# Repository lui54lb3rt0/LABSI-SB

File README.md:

# LABSI Project
## Description of project
This project has made part of the LABSI Class of my BSc in Electrical and Computer Engineer degree and consists of a self-balancing robot.

## The robot :robot: 

The robot has made with several components from old label printers and mechanical trash.

The robot has two wheels attached to the stepper motors that are capable to move forward and backward the robot with PWM generated in the function of GYRO and Accelerometer positions from a PID controller developed to the uC.

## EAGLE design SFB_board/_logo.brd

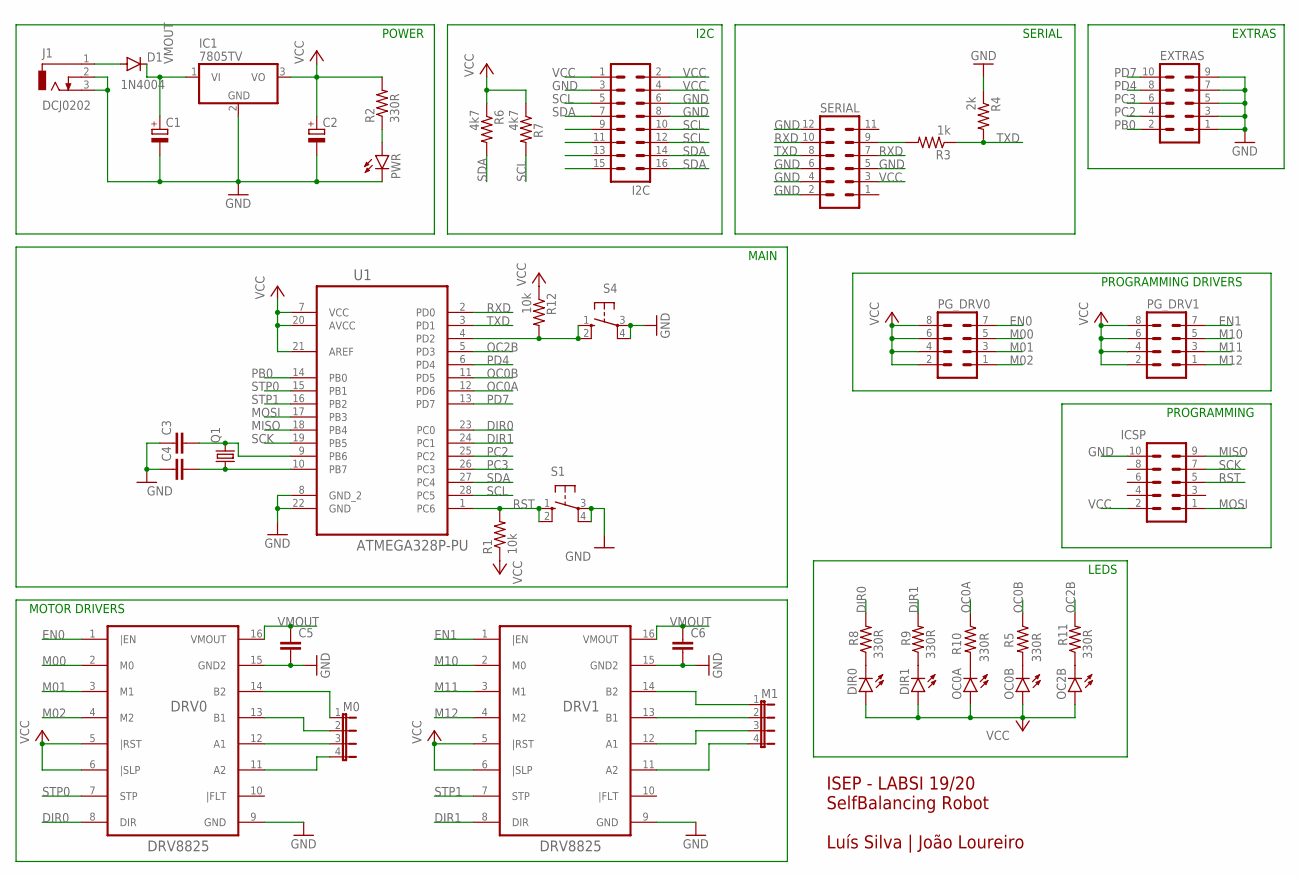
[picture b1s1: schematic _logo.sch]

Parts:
C1, C2: CPOL-EUB45181A; B45181A
C3, C4: C5/3; C5B3
C5, C6: C2.5/2; C2.5-2
D1: 1N4004; DO41-10
DIR0, DIR1: LED3MM
DRV0, DRV1: DRV8825
EXTRAS: ML10
I2C: MA08-2
IC1: 7805TV; TO220V
ICSP: ML10
J1: DCJ0202
M0, M1: JP4E; JP4
OC0A, OC0B, OC2B: LED3MM
PG_DRV0, PG_DRV1: MA04-2
PWR: LED3MM
Q1: CRYSTALHC49S; HC49/S
R1, R12: 10k; 0207/10
R2, R5, R8, R9, R10, R11: 330R; 0207/10
R3: 1k; 0207/10
R4: 2k; 0207/10
R6, R7: 4k7; 0207/10
S1, S4: 10-XX; B3F-10XX
SERIAL: MA06-2
U1: ATMEGA328P-PU; DIP254P762X457-28

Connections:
DIR0: DRV0.8 (DIR), R8.2, U1.23 (PC0)
DIR1: DRV1.8 (DIR), R9.2, U1.24 (PC1)
EN0: DRV0.1 (|EN), PG_DRV0.7
EN1: DRV1.1 (|EN), PG_DRV1.7
GND: C1.-, C2.-, C3.1, C4.1, C5.2, C6.2, DRV0.9 (GND), DRV0.15 (GND2), DRV1.9 (GND), DRV1.15 (GND2), EXTRAS.1, EXTRAS.3, EXTRAS.5, EXTRAS.7, EXTRAS.9, I2C.3, I2C.6, I2C.8, IC1.2 (GND), ICSP.10, J1.2, J1.3, PWR.K (C), R4.1, S1.3, S1.4 (P1), S4.3, S4.4 (P1), SERIAL.2, SERIAL.4, SERIAL.5, SERIAL.6, SERIAL.12, U1.8 (GND_2), U1.22 (GND)
M00: DRV0.2 (M0), PG_DRV0.5
M01: DRV0.3 (M1), PG_DRV0.3
M02: DRV0.4 (M2), PG_DRV0.1
M10: DRV1.2 (M0), PG_DRV1.5
M11: DRV1.3 (M1), PG_DRV1.3
M12: DRV1.4 (M2), PG_DRV1.1
MISO: ICSP.9, U1.18 (PB4)
MOSI: ICSP.1, U1.17 (PB3)
unnamed: DRV0.14 (B2), M0.1
unnamed: PWR.A, R2.1
unnamed: D1.A, J1.1
unnamed: C4.2, Q1.1, U1.10 (PB7)
unnamed: C3.2, Q1.2, U1.9 (PB6)
unnamed: R3.2, SERIAL.9
unnamed: OC0B.K (C), R5.2
unnamed: DIR0.K (C), R8.1
unnamed: DIR1.K (C), R9.1
unnamed: OC0A.K (C), R10.2
unnamed: OC2B.K (C), R11.1
unnamed: DRV0.13 (B1), M0.2
unnamed: DRV0.12 (A1), M0.3
unnamed: DRV0.11 (A2), M0.4
unnamed: DRV1.14 (B2), M1.1
unnamed: DRV1.13 (B1), M1.2
unnamed: DRV1.12 (A1), M1.3
unnamed: DRV1.11 (A2), M1.4
OC0A: R10.1, U1.12 (PD6)
OC0B: R5.1, U1.11 (PD5)
OC2B: R11.2, U1.5 (PD3)
PB0: EXTRAS.2, U1.14 (PB0)
PC2: EXTRAS.4, U1.25 (PC2)
PC3: EXTRAS.6, U1.26 (PC3)
PD4: EXTRAS.8, U1.6 (PD4)
PD7: EXTRAS.10, U1.13 (PD7)
RST: ICSP.5, R1.2, S1.1 (S), S1.2 (S1), U1.1 (PC6)
RST1: R12.2, S4.1 (S), S4.2 (S1), U1.4 (PD2)
RXD: SERIAL.7, SERIAL.10, U1.2 (PD0)
SCK: ICSP.7, U1.19 (PB5)
SCL: I2C.5, I2C.10, I2C.12, R7.2, U1.28 (PC5)
SDA: I2C.7, I2C.14, I2C.16, R6.2, U1.27 (PC4)
STP0: DRV0.7 (STP), U1.15 (PB1)
STP1: DRV1.7 (STP), U1.16 (PB2)
TXD: R3.1, R4.2, SERIAL.8, U1.3 (PD1)
VCC: C2.+, DIR0.A, DIR1.A, DRV0.5 (|RST), DRV0.6 (|SLP), DRV1.5 (|RST), DRV1.6 (|SLP), I2C.1, I2C.2, I2C.4, IC1.3 (VO), ICSP.2, OC0A.A, OC0B.A, OC2B.A, PG_DRV0.2, PG_DRV0.4, PG_DRV0.6, PG_DRV0.8, PG_DRV1.2, PG_DRV1.4, PG_DRV1.6, PG_DRV1.8, R1.1, R2.2, R6.1, R7.1, R12.1, SERIAL.3, U1.7 (VCC), U1.20 (AVCC), U1.21 (AREF)
VMOUT: C1.+, C5.1, C6.1, D1.C, DRV0.16 (VMOUT), DRV1.16 (VMOUT), IC1.1 (VI)

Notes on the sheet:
POWER
PROGRAMMING
ISEP - LABSI 19/20 SelfBalancing Robot Luís Silva | João Loureiro
I2C
SERIAL
EXTRAS
PROGRAMMING DRIVERS
LEDS
MAIN
MOTOR DRIVERS

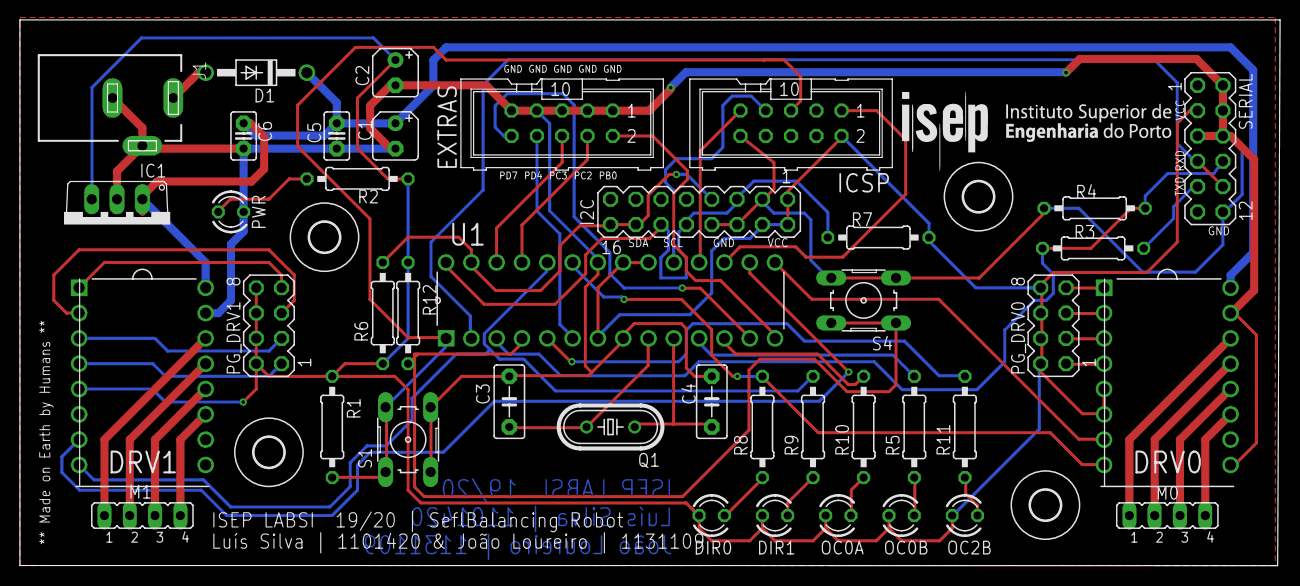
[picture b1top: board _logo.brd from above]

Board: 2 copper layers, 126.5 x 54.8 mm, 45 parts (0 on the bottom side), 50 nets.

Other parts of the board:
U$1, U$2, U$3, U$4: 3,0

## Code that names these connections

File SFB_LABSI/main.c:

/********************************************************
Language            :      C
Year                :      2019/2020
Class               :      LABSI
Authors             :      Luis Silva | Joao Loureiro
E-mail              :      1101420@isep.ipp.pt | 1131109@isep.ipp.pt
*********************************************************/

#define F_CPU 16000000UL								/* Define CPU clock Frequency e.g. here its 16MHz */
#include <avr/io.h>										/* Include AVR std. library file */
#include <avr/interrupt.h>								/* Include AVR interrupt library file */
#include <util/delay.h>									/* Include delay header file */
#include <inttypes.h>									/* Include integer type header file */
#include <stdlib.h>										/* Include standard library file */
#include <stdio.h>
#include <stdint.h>
#include "MPU6050_res_define.h"							/* Include MPU6050 register define file */
#include "I2C_Master_H_file.h"							/* Include I2C Master header file */

typedef struct USARTRX
{
	char receiver_buffer;
	unsigned char status;
	unsigned char receive 	: 1;
	unsigned char error	: 1;

}USARTRX_st;

volatile USARTRX_st rxUSART = {0,0,0,0};
char TxBuffer[50];
char float_[10];

/* Functions */

void SendMessage(char * buffer)
{
	unsigned char i=0;
	while(buffer[i]!='\0')
	{
		while((UCSR0A & 1<<UDRE0)==0);
		UDR0=buffer[i];
		i++;
	}
}

volatile uint8_t timerFlag = 0;
volatile float Acc_x,Acc_y,Acc_z,Temperature,Gyro_x,Gyro_y,Gyro_z;
volatile int ledCounter = 0;

float Acceleration_angle[2];
float Gyro_angle[2];
float Total_angle[2];

float elapsedTime = 0.001408;							//TS - time sample
float rad_to_deg = 180/3.141592654;

int PWM, error, previous_error;
float pid_p=0;
float pid_i=0;
float pid_d=0;
float pid_tot=0;
float previous_pid_tot = 0;

/////////////////PID CONSTANTS/////////////////
float kp = 0;
float ki = 0;
float kd = 0;
///////////////////////////////////////////////

float desired_angle = 0;								//This is the angle in which we want the balance to stay steady

/* Functions start here */
void inic()
{
	
	DDRC = 0x0F;										// Set PC0 & PC1 as output to Motor direction & scope test probes
	DDRB = 0x06;										// Set PB1 and PB2 as output OC1A & OC1B
	DDRD = (1<<DDD3) | (1<<DDD4) | (1<<DDD5) | (1<<DDD6) ;

	PORTD = (0<<DDD2) | (1<<DDD3)  | (1<<DDD5) | (1<<DDD6);
	PORTC = 0b00000011;

	/* Timer 1 */
	TCCR1A = ((1 << COM1A0) | (1 << COM1B0));			// Enable OC1A e OC1B to motors
	TCCR1B = ((1 << CS12) | (1 << WGM12));				// CLKIO/256 (From prescaler) | Mode CTC
	OCR1A = 65535;										// motor speed right
	OCR1B = 65535;										// motor speed left


	/* Timer 2 */
	TCCR2A = (1<<WGM21);								// MODE CTC
	TCCR2B = ((1 << CS21) | (1 << CS22));				// CLKIO/256 (From prescaler)
	TIMSK2 = (1 << OCIE2A);								// Enable TIMER0
	OCR2A = 88;											// ~0.001088s  ~900Hz    68

	/* USART */
	UBRR0H=0;
	UBRR0L=51;											// BAUDRATE 38400
	UCSR0A=(1<<U2X0);									// Double Speed
	UCSR0B=(1<<RXCIE0)|(1<<RXEN0)|(1<<TXEN0);			// RX Complete Interrupt Enable, Receiver Enable; transmite Enable
	UCSR0C=(1<<UCSZ01)|(1<<UCSZ00);						// 8 bits
	
	sei();
	
	sprintf(TxBuffer, "Init successfully!!!\r\n");
	SendMessage(TxBuffer);

}

void MPU6050_Init()                                     /* Gyro initialization function */
{
	_delay_ms(250);										/* Power up time >100ms */
	I2C_Start_Wait(0xD0);								/* Start with device write address */
	I2C_Write(SMPLRT_DIV);								/* Write to sample rate register */
	I2C_Write(0x07);									/* 1KHz sample rate */
	I2C_Stop();

	I2C_Start_Wait(0xD0);
	I2C_Write(PWR_MGMT_1);                              /* Write to power management register */
	I2C_Write(0x01);                                    /* X axis gyroscope reference frequency */
	I2C_Stop();

	I2C_Start_Wait(0xD0);
	I2C_Write(CONFIG);                                  /* Write to Configuration register */
	I2C_Write(0x00);                                    /* Fs = 8KHz */
	I2C_Stop();

	I2C_Start_Wait(0xD0);
	I2C_Write(GYRO_CONFIG);								/* Write to Gyro configuration register */
	I2C_Write(0x18);                                    /* Full scale range +/- 2000 degree/C */
	I2C_Stop();

	I2C_Start_Wait(0xD0);
	I2C_Write(INT_ENABLE);								/* Write to interrupt enable register */
	I2C_Write(0x01);
	I2C_Stop();
}

void MPU_Start_Loc()
{
	I2C_Start_Wait(0xD0);								/* I2C start with device write address */
	I2C_Write(ACCEL_XOUT_H);							/* Write start location address from where to read */
	I2C_Repeated_Start(0xD1);							/* I2C start with device read address */
}

void Read_RawValue()
{
	
	MPU_Start_Loc();            /* Read Gyro values */
	Acc_x = (((int)I2C_Read_Ack()<<8) | (int)I2C_Read_Ack());
	Acc_y = (((int)I2C_Read_Ack()<<8) | (int)I2C_Read_Ack());
	Acc_z = (((int)I2C_Read_Ack()<<8) | (int)I2C_Read_Ack());
	Gyro_x = (((int)I2C_Read_Ack()<<8) | (int)I2C_Read_Ack());
	Gyro_y = (((int)I2C_Read_Ack()<<8) | (int)I2C_Read_Ack());
	Gyro_z = (((int)I2C_Read_Ack()<<8) | (int)I2C_Read_Nack());
	I2C_Stop();

}

void AngleCalc()
{
	//---ACC  Y---
	Acceleration_angle[1] = atan(-1*(Acc_x/16384.0)/sqrt(pow((Acc_y/16384.0),2) + pow((Acc_z/16384.0),2)))*rad_to_deg;

	//---GYRO Y---
	Gyro_angle[1] = Gyro_y/131.0;
	
	//Complementary Filter
	//---Y axis angle--- Pitch
	Total_angle[1] = 0.98 *(Total_angle[1] + Gyro_angle[1]*elapsedTime) + 0.02*Acceleration_angle[1];
}

float sat(float _pid, int umin, int umax)
{
	if (_pid <= umin)
	{
		_pid = umin;
	}

	if (_pid >= umax)
	{
		_pid = umax;
	}
	return _pid;
}

void PID()
{
	error = Total_angle[1] - desired_angle;
	
	pid_i =+ki*(error+previous_error);
	pid_i = sat(pid_i,-1.5,2);
	pid_tot = previous_pid_tot + kp* (error-previous_error) + pid_i;
	
	//change motors direction
	if (error < 0)
	{
		PORTC = 0b00000000;
	}
	if (error >= 0)
	{
		PORTC = 0b00000011;
	}
	
	pid_tot = sat(pid_tot,-9,9);		//-10 10
	
	previous_error = error;
	previous_pid_tot = pid_tot;
	
}


int main()
{
	inic();                                              // Main configurations
	_delay_ms(500);
	I2C_Init();                                          // Initialize I2C
	MPU6050_Init();                                      // Initialize MPU6050
	desired_angle = 0;
	kp =0.55;
	ki = ((kp/0.9)*(elapsedTime/2));

	while(1)
	{
		//Set SETPOINT
		if((PIND & (1 << PIND2)) == 0 ) {
			OCR1A = 65535;
			OCR1B = 65535;
			desired_angle = Total_angle[1];
		}
		
		if (timerFlag==1)
		{
			Read_RawValue();							// Read gyro and acc from MPU6050
			AngleCalc();
			
			PID();
			
			PWM = 40.302*exp(-0.31*abs(pid_tot));		// Works well
			if ((error > -0.05) && (error <= 0.05)) PWM =10800;
			
			if ( (Total_angle[1] >= 0) && (Total_angle[1] <= 0.5)) {
				PWM = 65000;
			}
			else if ((Total_angle[1] >= -0.5) && (Total_angle[1] <= 0)) {
				PWM = 65000;
			}
			
			if ((Total_angle[1]>30) | (Total_angle[1]<-30))
			{
				PWM = 65535;
				pid_tot=0;
				pid_i=0;
				previous_error=0;
				previous_pid_tot=0;
			}


			if (TCNT1 >= PWM){
				TCNT1 = 0;
				OCR1A = PWM;
				OCR1B = PWM;
			}
			else
			{
				OCR1A = PWM;
				OCR1B = PWM;
			}
			
			timerFlag=0;
		}
	}
}


/* Interrupts */
ISR(TIMER2_COMPA_vect)
{
	
	if (timerFlag==0)
	{
		timerFlag=1;
	}
	if (ledCounter==500) {
		PORTD ^= (1<<DDD3);
		ledCounter = 0;
	}
	ledCounter ++;
}

ISR (USART_RX_vect)
{
	rxUSART.status = UCSR0A;
	if(rxUSART.status & ((1<<FE0) | (1<<DOR0) | (1<<UPE0)))
	rxUSART.error = 1;
	rxUSART.receiver_buffer = UDR0;
	rxUSART.receive = 1;
}

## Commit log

2020-01-04 Organize code
